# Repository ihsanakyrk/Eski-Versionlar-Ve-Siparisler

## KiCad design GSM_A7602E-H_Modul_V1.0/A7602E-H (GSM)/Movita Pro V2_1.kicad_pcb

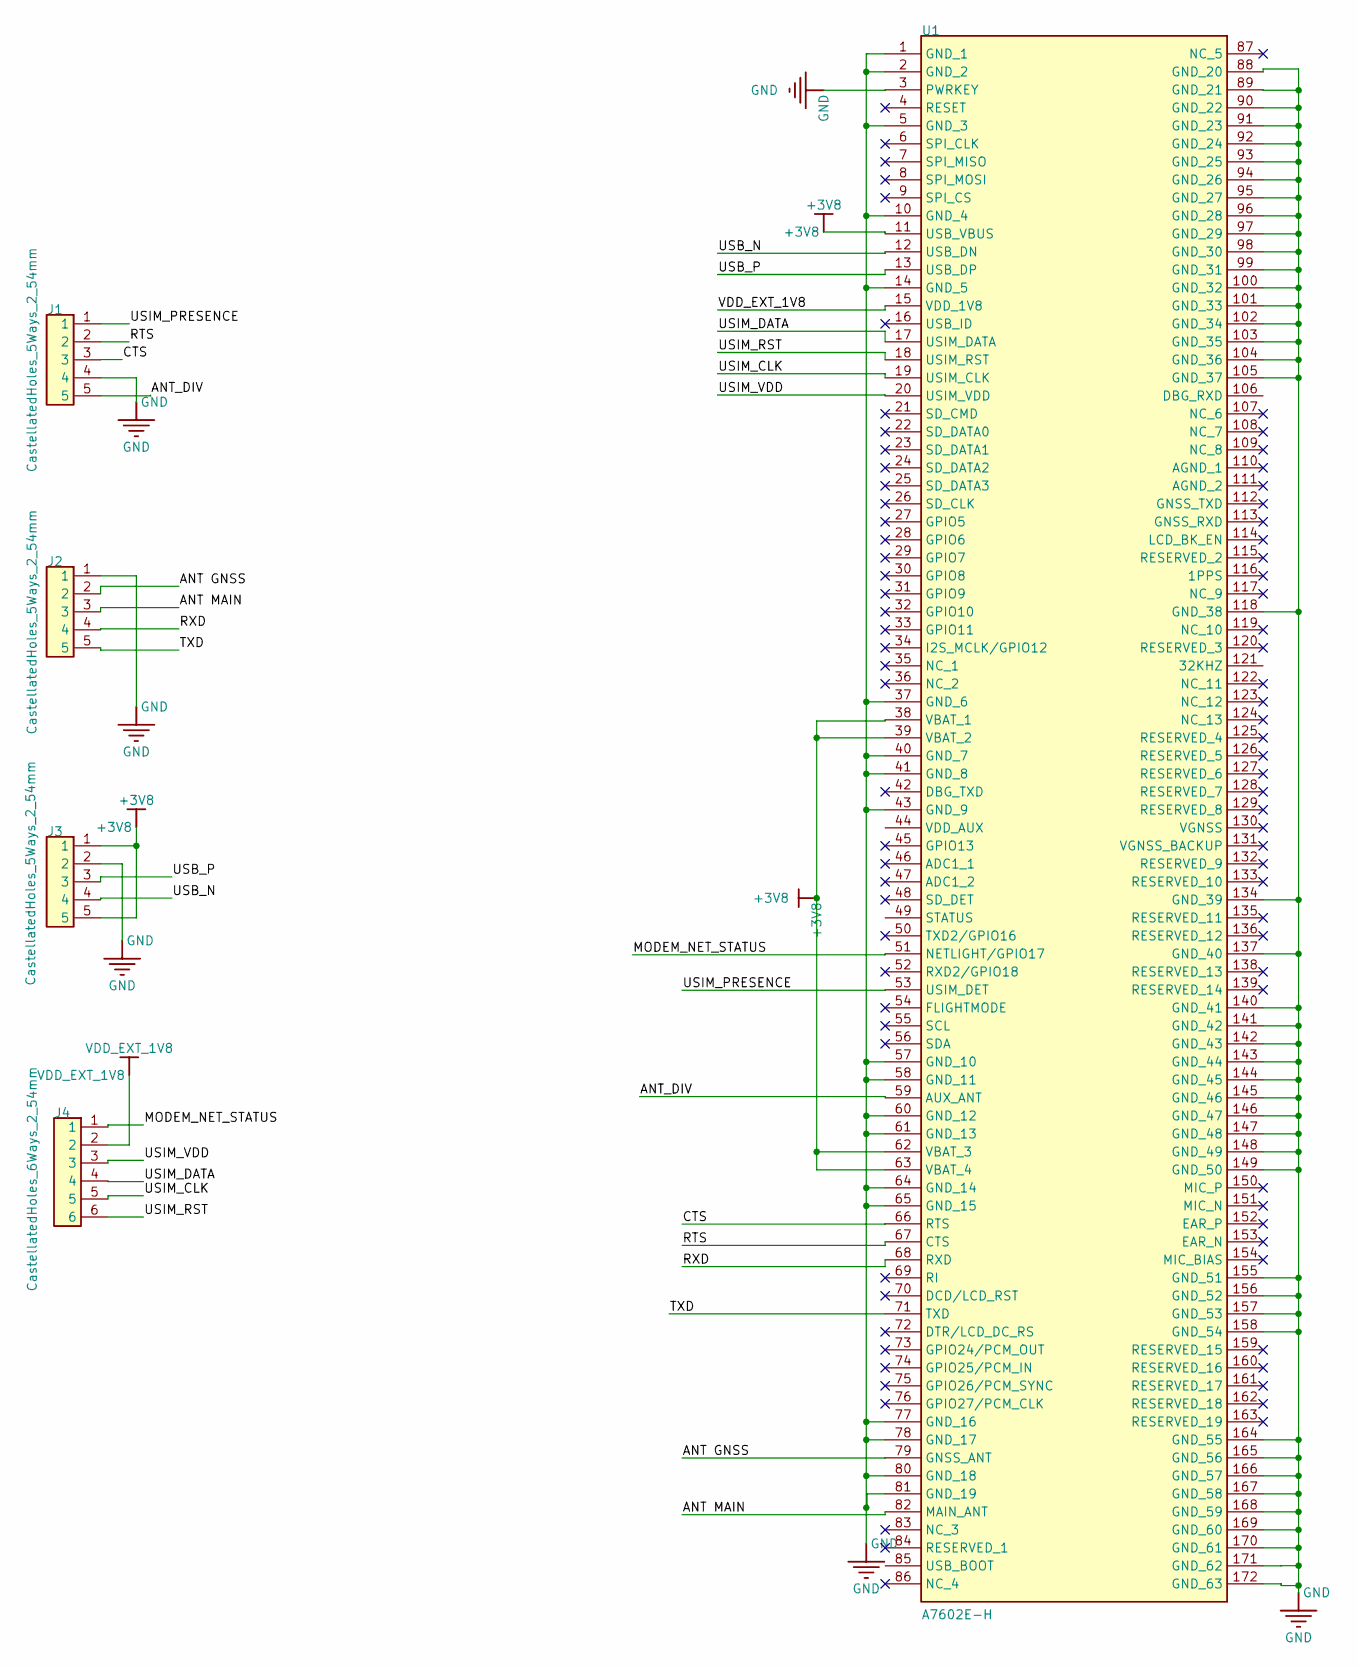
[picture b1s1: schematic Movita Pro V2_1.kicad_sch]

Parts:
J1, J2, J3: CastellatedHoles_5Ways_2_54mm; Castelled Pin Header 1x5 Ways 2.54
J4: CastellatedHoles_6Ways_2_54mm; Castelled Pin Header 1x6 Ways 2.54
U1: A7602E-H; A7602EH; MANUFACTURER_PART_NUMBER A7602E-H; MOUSER PART NUMBER *

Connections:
+3V8: J3.1, J3.5, U1.11 (USB_VBUS), U1.38 (VBAT_1), U1.39 (VBAT_2), U1.62 (VBAT_3), U1.63 (VBAT_4)
/ANT GNSS: J2.2, U1.79 (GNSS_ANT)
/ANT MAIN: J2.3, U1.82 (MAIN_ANT)
/ANT_DIV: J1.5, U1.59 (AUX_ANT)
/CTS: J1.3, U1.66 (RTS)
/MODEM_NET_STATUS: J4.1, U1.51 (NETLIGHT/GPIO17)
/RTS: J1.2, U1.67 (CTS)
/RXD: J2.4, U1.68 (RXD)
/TXD: J2.5, U1.71 (TXD)
/USB_N: J3.4, U1.12 (USB_DN)
/USB_P: J3.3, U1.13 (USB_DP)
/USIM_CLK: J4.5, U1.19 (USIM_CLK)
/USIM_DATA: J4.4, U1.17 (USIM_DATA)
/USIM_PRESENCE: J1.1, U1.53 (USIM_DET)
/USIM_RST: J4.6, U1.18 (USIM_RST)
/USIM_VDD: J4.3, U1.20 (USIM_VDD)
GND: J1.4, J2.1, J3.2, U1.1 (GND_1), U1.2 (GND_2), U1.3 (PWRKEY), U1.5 (GND_3), U1.10 (GND_4), U1.14 (GND_5), U1.37 (GND_6), U1.40 (GND_7), U1.41 (GND_8), U1.43 (GND_9), U1.57 (GND_10), U1.58 (GND_11), U1.60 (GND_12), U1.61 (GND_13), U1.64 (GND_14), U1.65 (GND_15), U1.77 (GND_16), U1.78 (GND_17), U1.80 (GND_18), U1.81 (GND_19), U1.88 (GND_20), U1.89 (GND_21), U1.90 (GND_22), U1.91 (GND_23), U1.92 (GND_24), U1.93 (GND_25), U1.94 (GND_26), U1.95 (GND_27), U1.96 (GND_28), U1.97 (GND_29), U1.98 (GND_30), U1.99 (GND_31), U1.100 (GND_32), U1.101 (GND_33), U1.102 (GND_34), U1.103 (GND_35), U1.104 (GND_36), U1.105 (GND_37), U1.118 (GND_38), U1.134 (GND_39), U1.137 (GND_40), U1.140 (GND_41), U1.141 (GND_42), U1.142 (GND_43), U1.143 (GND_44), U1.144 (GND_45), U1.145 (GND_46), U1.146 (GND_47), U1.147 (GND_48), U1.148 (GND_49), U1.149 (GND_50), U1.155 (GND_51), U1.156 (GND_52), U1.157 (GND_53), U1.158 (GND_54), U1.164 (GND_55), U1.165 (GND_56), U1.166 (GND_57), U1.167 (GND_58), U1.168 (GND_59), U1.169 (GND_60), U1.170 (GND_61), U1.171 (GND_62), U1.172 (GND_63)
VDD_EXT_1V8: J4.2, U1.15 (VDD_1V8)

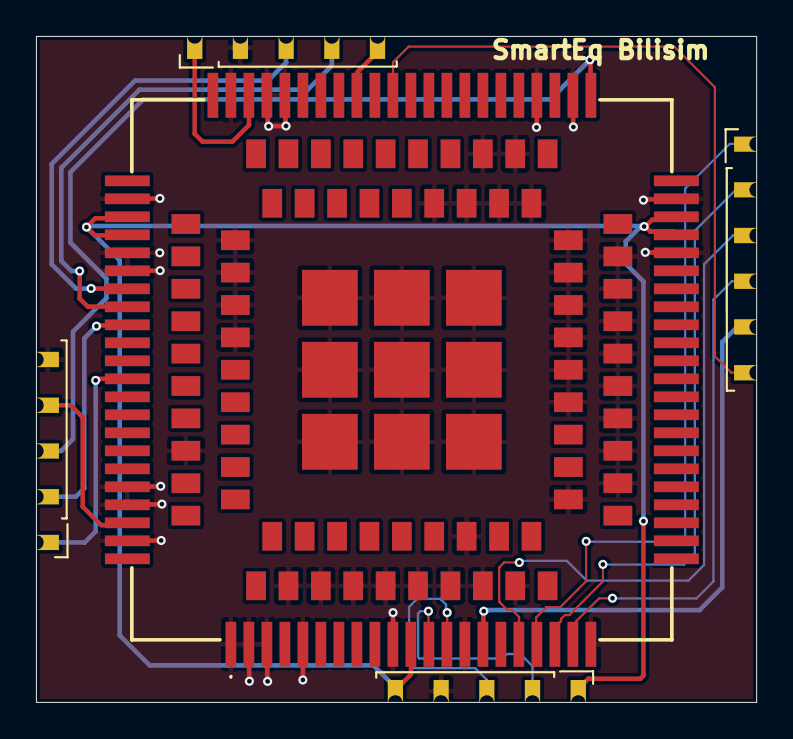
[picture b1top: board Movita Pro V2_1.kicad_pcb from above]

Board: 2 copper layers, 40.0 x 37.0 mm, 5 parts (0 on the bottom side), 18 nets.

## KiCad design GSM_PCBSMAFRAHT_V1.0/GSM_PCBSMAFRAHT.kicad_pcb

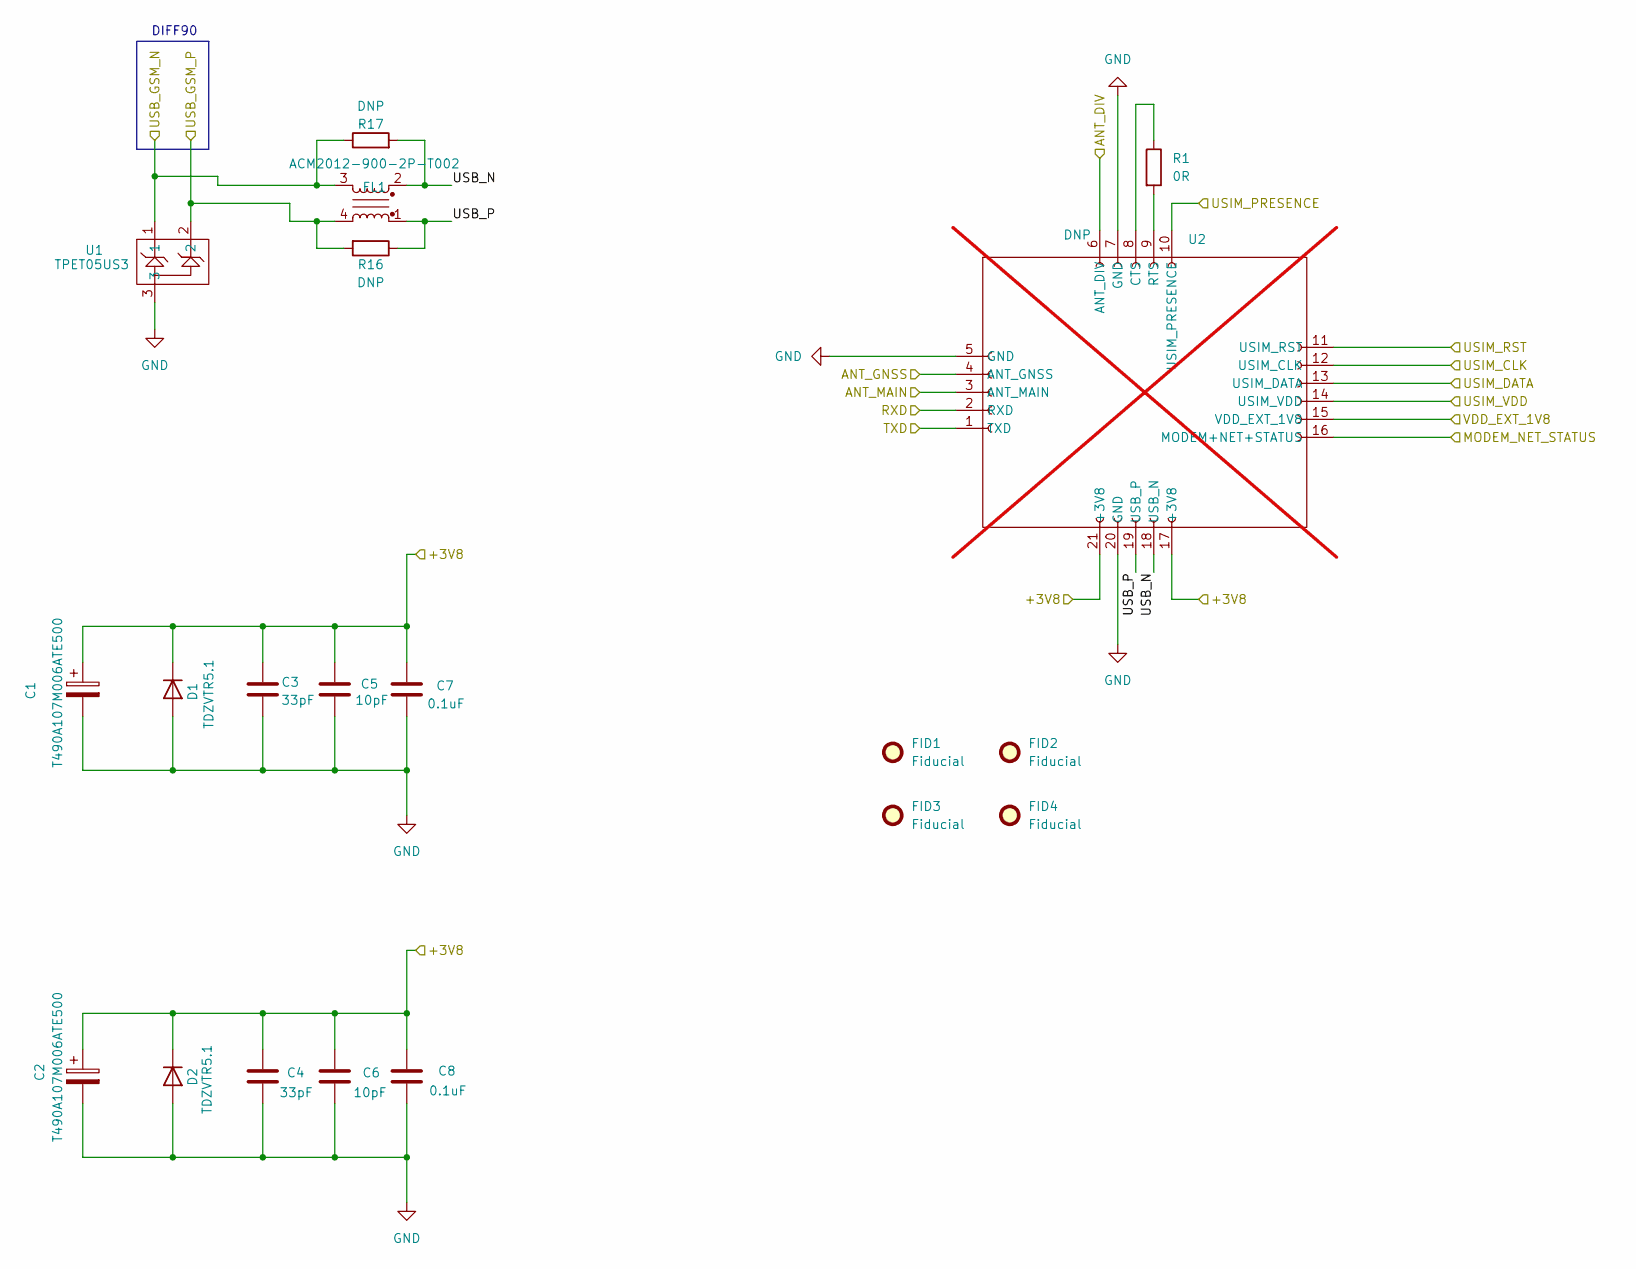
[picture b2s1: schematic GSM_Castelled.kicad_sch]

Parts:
C1, C2: T490A107M006ATE500; T490A; MPN T490A107M006ATE500
C3, C4: 33pF; C_0603_1608Metric
C5, C6: 10pF; C_0603_1608Metric
C7, C8: 0.1uF; C_0603_1608Metric
D1, D2: TDZVTR5.1; MPN TDZVTR5.1
FID1, FID2, FID3, FID4: Fiducial; Fiducial_0.5mm_Mask1.5mm
FL1: ACM2012-900-2P-T002; MPN ACM2012-900-2P-T002
R1: 0R; R_0603_1608Metric
R16, R17: DNP; R_0603_1608Metric
U1: TPET05US3; MPN TPET05US3
U2: DNP; GSM_Castelled; not fitted

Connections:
/91228-3002/MODEM_NET_STATUS: U2.16 (MODEM+NET+STATUS); also elsewhere on the board
/91228-3002/RXD: U2.2 (RXD); also elsewhere on the board
/91228-3002/TXD: U2.1 (TXD); also elsewhere on the board
/91228-3002/USB_GSM_N: FL1.3, R17.1, U1.1; also elsewhere on the board
/91228-3002/USB_GSM_P: FL1.4, R16.2, U1.2; also elsewhere on the board
/91228-3002/USIM_CLK: U2.12 (USIM_CLK); also elsewhere on the board
/91228-3002/USIM_DATA: U2.13 (USIM_DATA); also elsewhere on the board
/91228-3002/USIM_PRESENCE: U2.10 (USIM_PRESENCE); also elsewhere on the board
/91228-3002/USIM_RST: U2.11 (USIM_RST); also elsewhere on the board
/91228-3002/USIM_VDD: U2.14 (USIM_VDD); also elsewhere on the board
/91228-3002/VDD_EXT_1V8: U2.15 (VDD_EXT_1V8); also elsewhere on the board
/GSM_Castelled/+3V8: C1.1, C2.1, C3.1, C4.1, C5.1, C6.1, C7.1, C8.1, D1.1 (K), D2.1 (K), U2.17 (+3V8), U2.21 (+3V8); also elsewhere on the board
/GSM_Castelled/ANT_DIV: U2.6 (ANT_DIV); also elsewhere on the board
/GSM_Castelled/ANT_GNSS: U2.4 (ANT_GNSS); also elsewhere on the board
/GSM_Castelled/ANT_MAIN: U2.3 (ANT_MAIN); also elsewhere on the board
/GSM_Castelled/USB_N: FL1.2, R17.2, U2.18 (USB_N)
/GSM_Castelled/USB_P: FL1.1, R16.1, U2.19 (USB_P)
GND: C1.2, C2.2, C3.2, C4.2, C5.2, C6.2, C7.2, C8.2, D1.2 (A), D2.2 (A), U1.3, U2.5 (GND), U2.7 (GND), U2.20 (GND); also elsewhere on the board
unnamed: R1.1, U2.8 (CTS)
unnamed: R1.2, U2.9 (RTS)

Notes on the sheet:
DIFF90

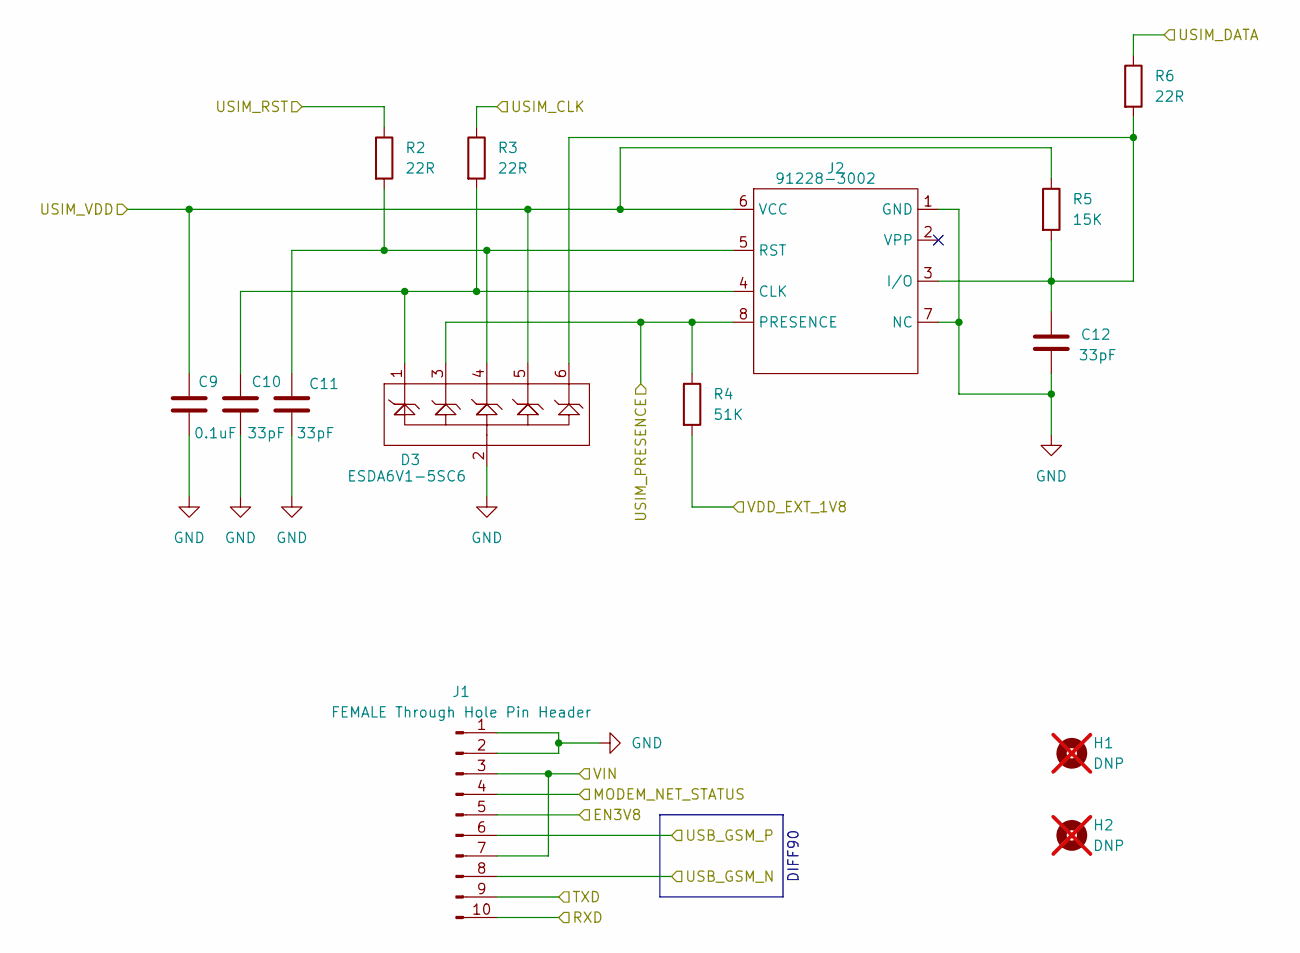
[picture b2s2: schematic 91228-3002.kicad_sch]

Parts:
C9: 0.1uF; C_0603_1608Metric
C10, C11, C12: 33pF; C_0603_1608Metric
D3: ESDA6V1-5SC6; MPN ESDA6V1-5SC6
H1, H2: DNP; Screw_Terminal_1x1; not fitted
J1: FEMALE Through Hole Pin Header; PinHeader_2x05_P2.00mm_Vertical
J2: 91228-3002; 912283002; MPN 91228-3002
R2, R3, R6: 22R; R_0603_1608Metric
R4: 51K; R_0603_1608Metric
R5: 15K; R_0603_1608Metric

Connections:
/91228-3002/EN3V8: J1.5; also elsewhere on the board
/91228-3002/MODEM_NET_STATUS: J1.4; also elsewhere on the board
/91228-3002/RXD: J1.10; also elsewhere on the board
/91228-3002/TXD: J1.9; also elsewhere on the board
/91228-3002/USB_GSM_N: J1.8; also elsewhere on the board
/91228-3002/USB_GSM_P: J1.6; also elsewhere on the board
/91228-3002/USIM_CLK: R3.1; also elsewhere on the board
/91228-3002/USIM_DATA: R6.1; also elsewhere on the board
/91228-3002/USIM_PRESENCE: D3.3, J2.8 (PRESENCE), R4.1; also elsewhere on the board
/91228-3002/USIM_RST: R2.1; also elsewhere on the board
/91228-3002/USIM_VDD: C9.1, D3.5, J2.6 (VCC), R5.1; also elsewhere on the board
/91228-3002/VDD_EXT_1V8: R4.2; also elsewhere on the board
/91228-3002/VIN: J1.3, J1.7; also elsewhere on the board
GND: C9.2, C10.2, C11.2, C12.2, D3.2, J1.1, J1.2, J2.1 (GND), J2.7 (NC); also elsewhere on the board
unnamed: C10.1, D3.1, J2.4 (CLK), R3.2
unnamed: C12.1, D3.6, J2.3 (I/O), R5.2, R6.2
unnamed: C11.1, D3.4, J2.5 (RST), R2.2

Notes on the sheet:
DIFF90

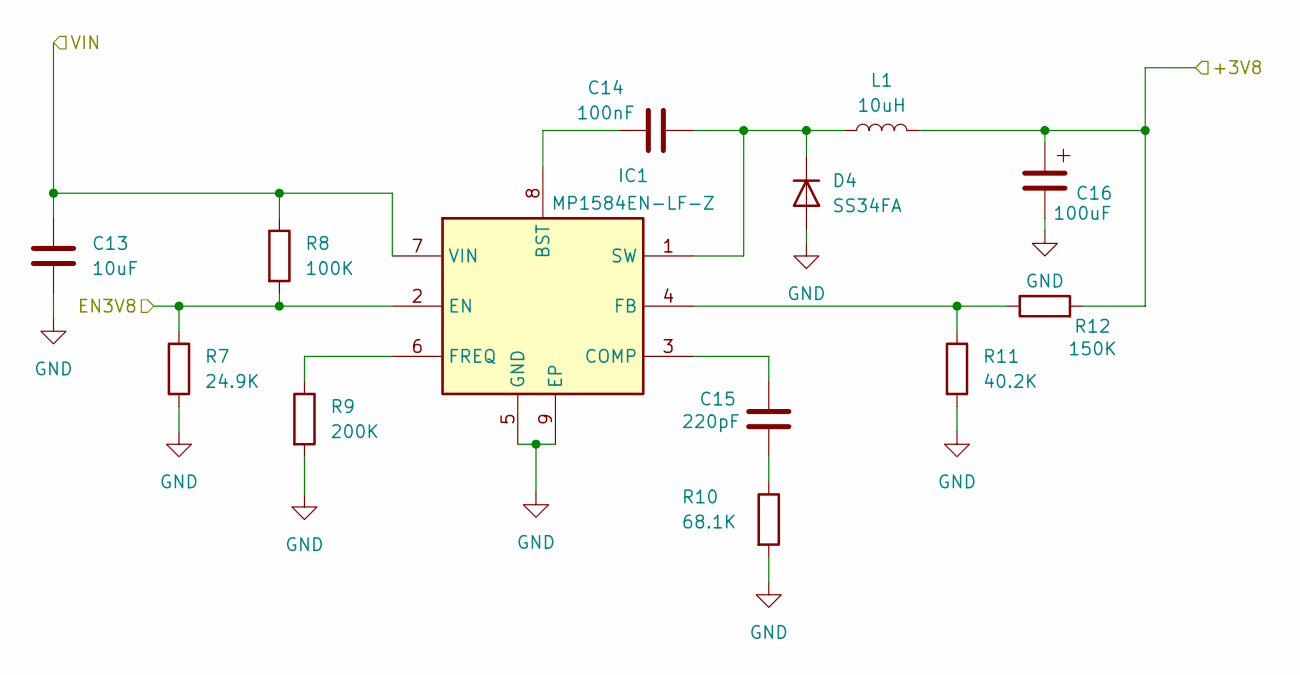
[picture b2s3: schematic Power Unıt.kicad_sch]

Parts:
C13: 10uF; C_1206_3216Metric
C14: 100nF; C_0603_1608Metric
C15: 220pF; C_0603_1608Metric
C16: 100uF; CP_Elec_5x5.4; MPN UWR1A101MCL1GB
D4: SS34FA; SS4FA; MPN SS34FA
IC1: MP1584EN-LF-Z; Manufacturer_Part_Number MP1584EN
L1: 10uH; L_7.3x7.3_H3.5; MPN CDRH74NP-100MC-B
R7: 24.9K; R_0603_1608Metric
R8: 100K; R_0603_1608Metric
R9: 200K; R_0603_1608Metric
R10: 68.1K; R_0603_1608Metric
R11: 40.2K; R_0603_1608Metric
R12: 150K; R_0603_1608Metric

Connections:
/91228-3002/EN3V8: IC1.2 (EN), R7.1, R8.2; also elsewhere on the board
/91228-3002/VIN: C13.1, IC1.7 (VIN), R8.1; also elsewhere on the board
/GSM_Castelled/+3V8: C16.1, L1.2, R12.2; also elsewhere on the board
GND: C13.2, C16.2, D4.2 (A), IC1.5 (GND), IC1.9 (EP), R7.2, R9.2, R10.2, R11.2; also elsewhere on the board
unnamed: C15.2, R10.1
unnamed: C14.2, D4.1 (K), IC1.1 (SW), L1.1
unnamed: C14.1, IC1.8 (BST)
unnamed: C15.1, IC1.3 (COMP)
unnamed: IC1.4 (FB), R11.1, R12.1
unnamed: IC1.6 (FREQ), R9.1

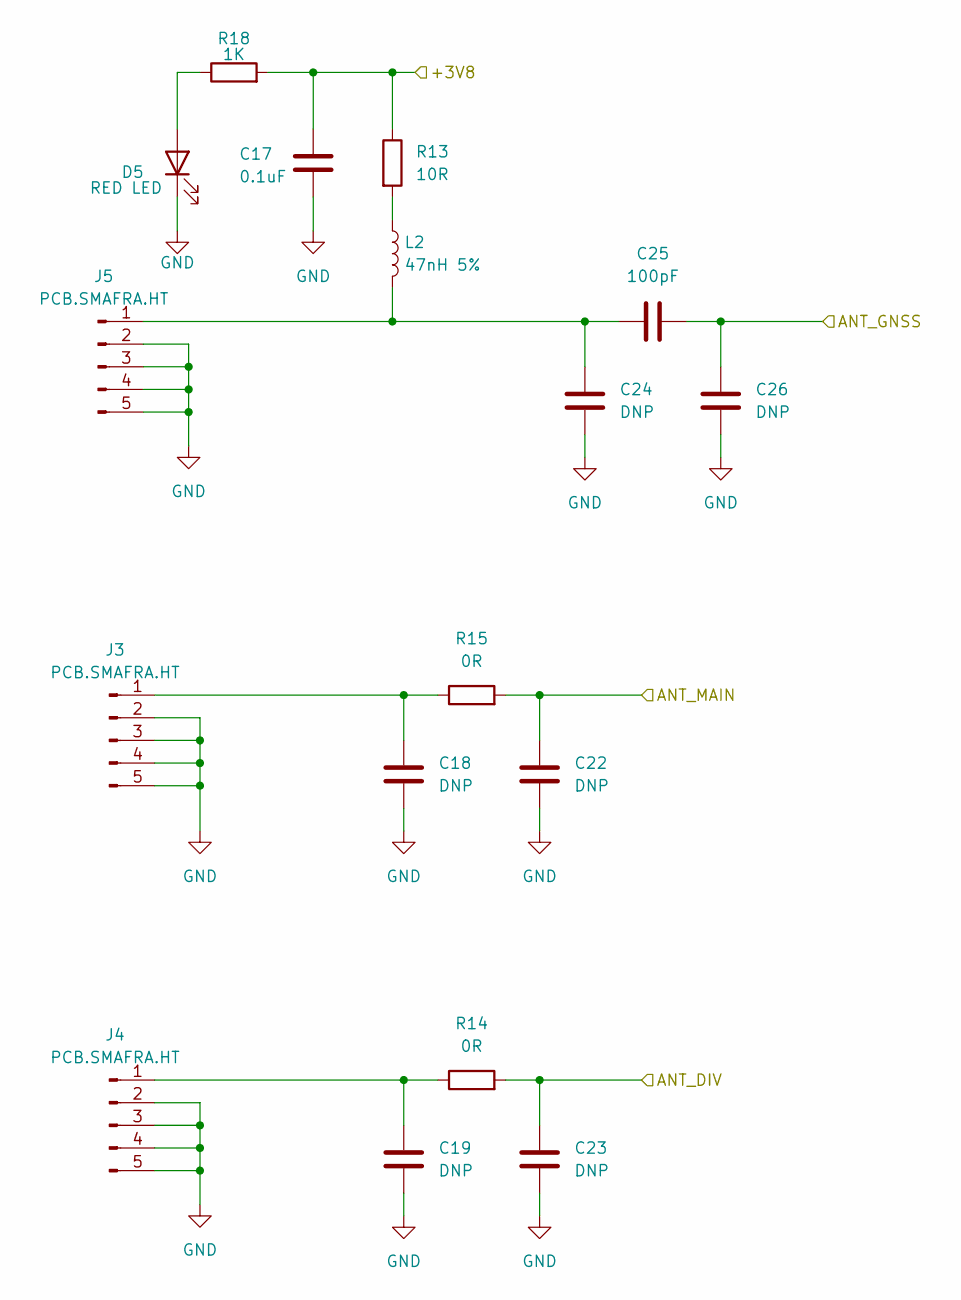
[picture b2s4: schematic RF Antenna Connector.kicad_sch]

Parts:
C17: 0.1uF; C_0603_1608Metric
C18, C19, C22, C23, C24, C26: DNP; C_0603_1608Metric
C25: 100pF; C_0603_1608Metric
D5: RED LED; LED_0805_2012Metric
J3, J4, J5: PCB.SMAFRA.HT; MPN Right angle SMA inner Hole
L2: 47nH 5%; L_0402_1005Metric; MPN LQG15HS47NJ02D
R13: 10R; R_0603_1608Metric
R14, R15: 0R; R_0603_1608Metric
R18: 1K; R_0603_1608Metric

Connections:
/GSM_Castelled/+3V8: C17.1, R13.1, R18.2; also elsewhere on the board
/GSM_Castelled/ANT_DIV: C22.1, R15.2; also elsewhere on the board
/GSM_Castelled/ANT_GNSS: C25.2, C26.1; also elsewhere on the board
/GSM_Castelled/ANT_MAIN: C23.1, R14.2; also elsewhere on the board
GND: C17.2, C18.1, C19.1, C22.2, C23.2, C24.1, C26.2, D5.1 (K), J3.2, J3.3, J3.4, J3.5, J4.2, J4.3, J4.4, J4.5, J5.2, J5.3, J5.4, J5.5; also elsewhere on the board
unnamed: D5.2 (A), R18.1
unnamed: C18.2, J3.1, R15.1
unnamed: C19.2, J4.1, R14.1
unnamed: C24.2, C25.1, J5.1, L2.2
unnamed: L2.1, R13.2

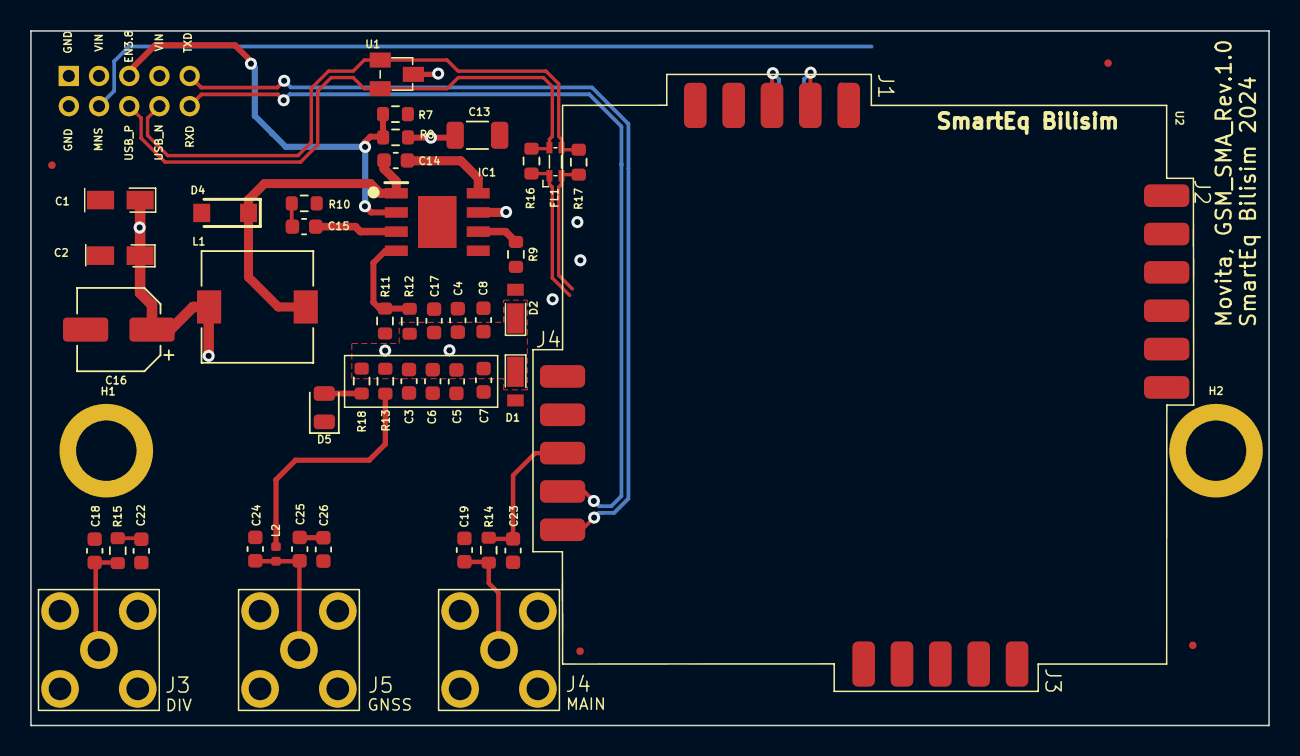
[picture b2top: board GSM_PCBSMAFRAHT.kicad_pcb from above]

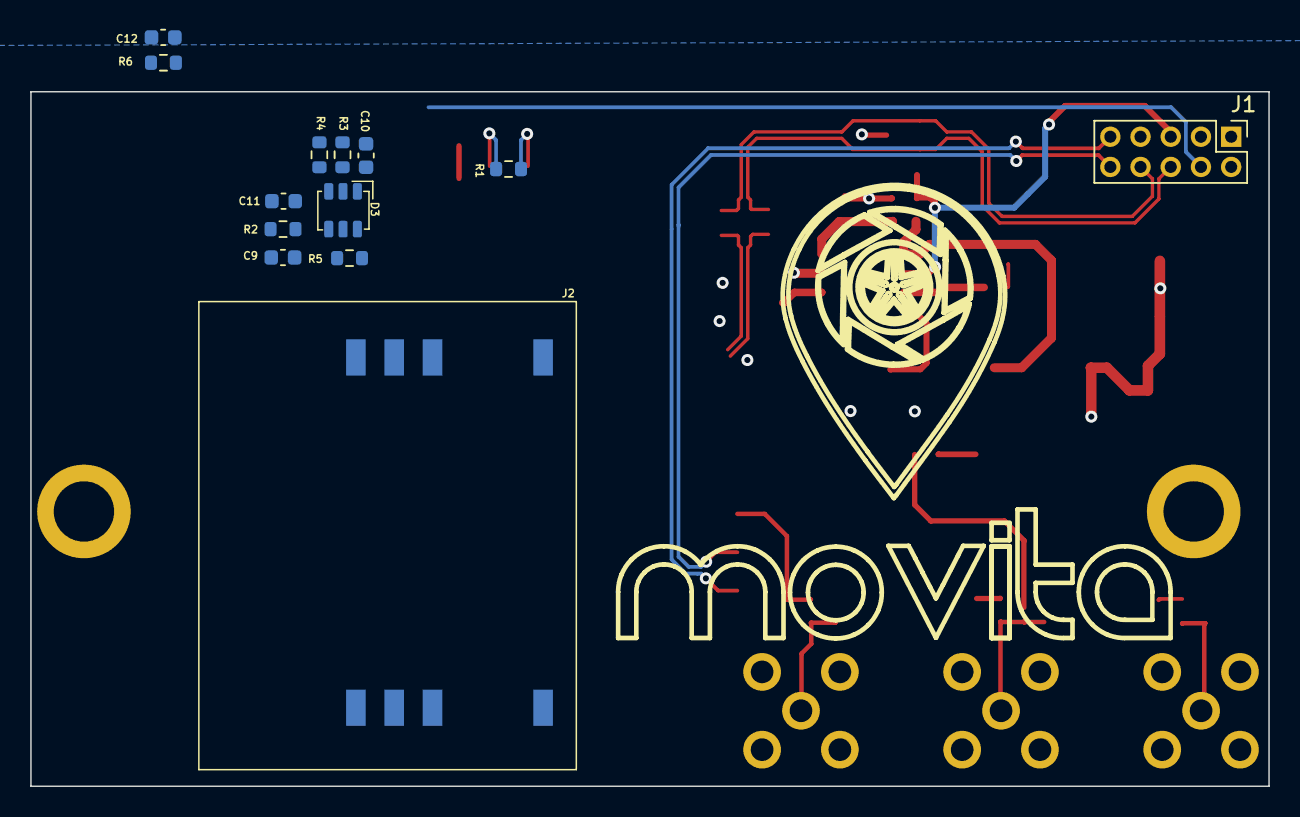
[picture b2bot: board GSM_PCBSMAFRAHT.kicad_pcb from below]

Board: 4 copper layers, 82.0 x 46.0 mm, 64 parts (13 on the bottom side), 36 nets.

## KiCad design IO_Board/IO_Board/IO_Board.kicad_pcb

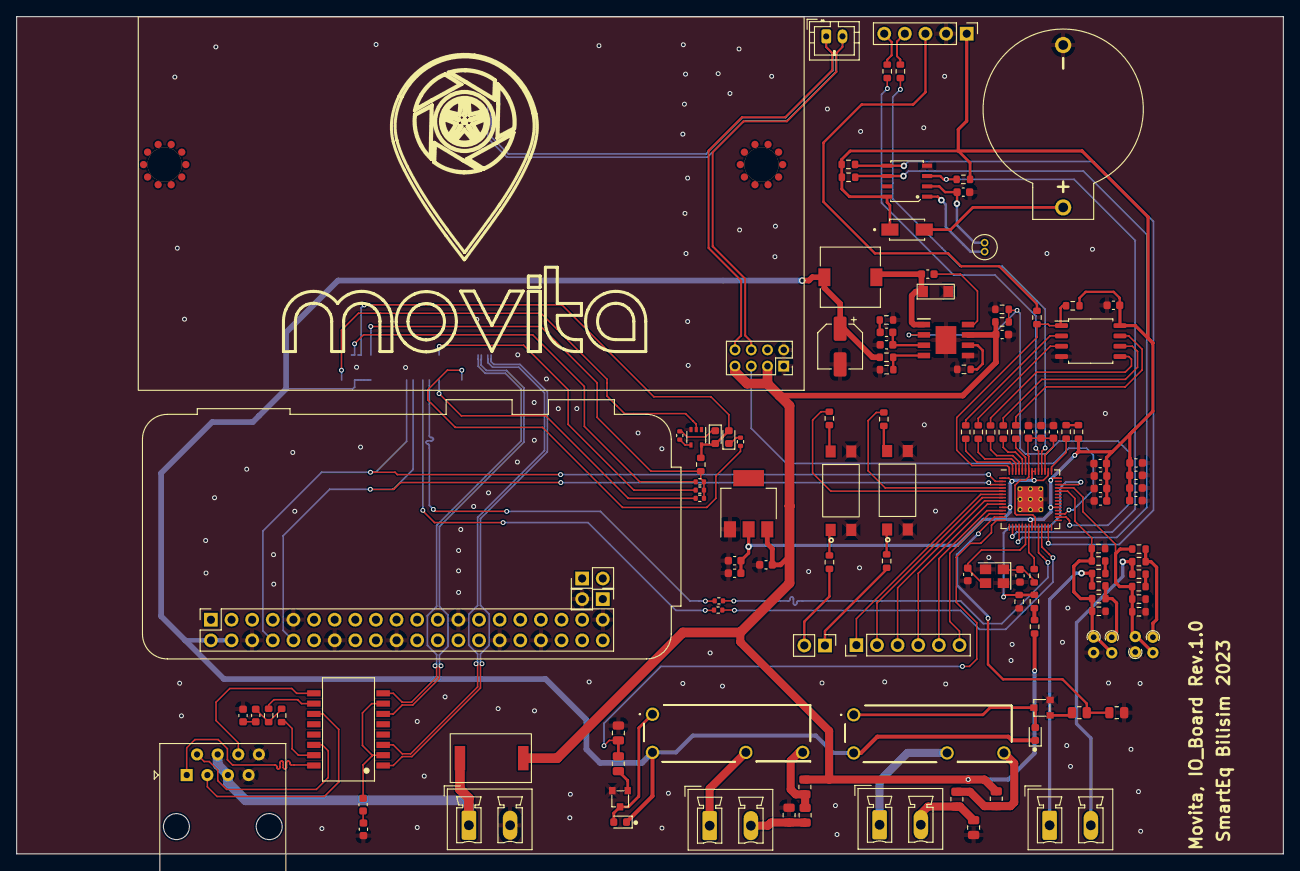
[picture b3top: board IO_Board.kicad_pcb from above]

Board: 2 copper layers, 156.0 x 103.1 mm, 131 parts (1 on the bottom side), 109 nets.

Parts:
C1, C2: 10uF; C_0603_1608Metric
C3, C12, C13, C16, C17, C18, C19, C20, C21, C22: 100nF; C_0603_1608Metric
C4: 150pF; C_0603_1608Metric
C5: DNP; C_0603_1608Metric
C6: 100uF; CP_Elec_5x5.4
C7: 22uF; C_0603_1608Metric
C8: 0.1uF; C_0603_1608Metric
C9: 1nF; C_0603_1608Metric
C10, C11: 27pF; C_0603_1608Metric
C14, C15: 1uF; C_0603_1608Metric
C23: 22pF; C_0603_1608Metric
C24, C25: 0.01uF; C_0603_1608Metric
C26, C27: 1000pF; C_0603_1608Metric
D1: SS34FA
D2: SS14; DIOM4325X250N
D3, D4: MRA4007T3G
D5: LED Green; LED_0603_1608Metric
D6: S6MC
D7: LED Red; LED_0603_1608Metric
IC1: MP1584EN; MP1584
J1: FEMALE Through Hole Pin Header; PinHeader_2x20_P2.54mm_Vertical
J2, J3: DNP; PinHeader_1x02_P2.54mm_Vertical
J4: JST_PH_B2B-PH-K_1x02_P2.00mm_Vertical
J5: FEMALE Through Hole Pin Header; PinHeader_1x02_P2.54mm_Vertical
J6, J8, J14, J15: KF2EDGR-Y-5.08-2P-Right Angle
J7: DNP; PinHeader_1x06_P2.54mm_Vertical
J9: MYOUNG BS-02-A1AJ010
J10, J11: M3x*0.5 L=8; Screw_terminal_shinbo
J12: FEMALE Through Hole Pin Header; PinSocket_2x04_P2.00mm_Vertical
J13: FEMALE Through Hole Pin Header; PinHeader_1x05_P2.54mm_Vertical
J16: RJ45; RJ45_Amphenol_54602-x08_Horizontal
K1, K2: DNP; HF46F_5-HS1
L1: 10uH; L_7.3x7.3_H3.5
Q1, Q2: MMBT2222ALT1G
R1, R2, R3, R4, R25: 1K; R_0603_1608Metric
R5, R6, R53: 0R; R_0603_1608Metric
R7, R8, R23, R55: DNP; R_0603_1608Metric
R9, R10, R15, R16: 100R; R_0603_1608Metric
R11, R13: 1.78K; R_0603_1608Metric
R12, R14: 220R; R_0603_1608Metric
R17: 2.2K; R_0603_1608Metric
R18, R19, R20: 100K; R_0603_1608Metric
R21: 40.2K; R_0603_1608Metric
R22: 210K; R_0603_1608Metric
R24: 10K; R_0603_1608Metric
R26, R27, R28, R29, R30, R33, R34: 27R; R_0603_1608Metric
R31: 200R; R_0603_1608Metric
R32: 1R; R_0603_1608Metric
R35: 4.7K; R_0603_1608Metric
R36, R37: 4.7K %5; R_0603_1608Metric
R38, R39, R44, R45: DNP; R_Axial_DIN0204_L3.6mm_D1.6mm_P1.90mm_Vertical
R40, R48: DNP; R_0805_2012Metric
R41, R42, R49, R50: 0R; R_0805_2012Metric
R43, R62: 1K; R_0402_1005Metric
R46, R51: 10K; R_0805_2012Metric
R47, R52: 1K; R_0805_2012Metric
R54, R63, R64: DNP; R_0402_1005Metric
R56: 725R; R_0603_1608Metric
R57: 275R; R_0603_1608Metric
R58, R60: 75R; R_0603_1608Metric
R59, R61: 2.2K 1%; R_0402_1005Metric
T1: H1102NL
U1, U2: PC817C_4PIN_SMD; PC817C SMD 4pin
U3: LM1117S-3.3; SOT-223
U4: W25Q128JVSIQ; W25Q128JVS
U5: RP2040; RP20400
U6: PCF8563
U7: DNP; Raspberry-Pi-4-Compute-Module
U8: 74LVC1G07SE-7; SOT-353_SC-70-5
Y1: TAXM12M4RLBDDT2T
Y2: ECS-3X8X

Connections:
3.3V: C7.1, C8.1, C9.1, C15.1, C16.1, C17.1, C18.1, C19.1, C20.1, C21.1, C22.1, D2.C, J13.1, R23.1, R31.1, R35.2, R36.2, R37.2, U3.2 (VO), U4.8 (VCC), U5.1 (IOVDD), U5.10 (IOVDD), U5.22 (IOVDD), U5.33 (IOVDD), U5.42 (IOVDD), U5.44 (VREG_IN), U5.48 (USB_VDD), U5.49 (IOVDD), U6.8 (VDD)
5V: C6.1, D3.1 (K), D4.1 (K), J1.2, J1.4, K1.2 (COIL_2), K2.2 (COIL_2), L1.2, R22.2, U7.77 (+5v_(Input)), U7.79 (+5v_(Input)), U7.81 (+5v_(Input)), U7.83 (+5v_(Input)), U7.85 (+5v_(Input)), U7.87 (+5v_(Input))
+1V1: C12.1, C13.1, C14.1, U5.23 (DVDD), U5.45 (VREG_VOUT), U5.50 (DVDD)
/CM4_GPIO/+1.8V: R54.1, U7.88 (+1.8v_(Output)), U7.90 (+1.8v_(Output))
/CM4_GPIO/+3.3v: D5.2 (A), D7.2 (A), R53.2, U7.84 (+3.3v_(Output)), U7.86 (+3.3v_(Output)), U8.5 (VCC)
/CM4_GPIO/CM4_SWCLK: R63.2, U5.24 (SWCLK)
/CM4_GPIO/CM4_SWDIO: R64.2, U5.25 (SWD)
/CM4_GPIO/GPIO_VREF: R53.1, R54.2, R59.1, R61.1, U7.78 (GPIO_VREF(1.8v/3.3v_Input))
/CM4_GPIO/ID_SC: R59.2, U7.35 (ID_SC)
/CM4_GPIO/ID_SD: R61.2, U7.36 (ID_SD)
/CM4_GPIO/USB2_N: J4.1, J12.8, U7.103 (USB2_N)
/CM4_GPIO/USB2_P: J4.2, J12.6, U7.105 (USB2_P)
/CM4_GPIO/VOUT_CAM: D6.2 (A), J8.1, J16.4, J16.5
/CM4_GPIO/nPWR_LED: U7.95 (nPI_LED_PWR), U8.2
/Connectors/Analog_Input1: J6.1, R5.2, R7.2
/Connectors/Analog_Input2: J6.2, R6.2, R8.2
/Connectors/GP4: J7.1, U5.6 (GPIO4)
/Connectors/GP5: J7.2, U5.7 (GPIO5)
/Connectors/GP6: J7.3, U5.8 (GPIO6)
/Connectors/GP7: J7.4, U5.9 (GPIO7)
/Connectors/GP8: J7.5, U5.11 (GPIO8)
/Connectors/GP9: J7.6, U5.12 (GPIO9)
/Connectors/GP26_AO: R9.1, R11.1, R12.1, R15.2, R38.2, R44.1, U5.38 (GPIO26_ADC0)
/Connectors/GP27_AO: R10.1, R13.1, R14.1, R16.2, R39.2, R45.2, U5.39 (GPIO27_ADC1)
/Connectors/GP28_AO: R56.1, R57.1, U5.40 (GPIO28_ADC2)
/Connectors/GP_2: R3.1, U5.4 (GPIO2)
/Connectors/GP_3: R4.1, U5.5 (GPIO3)
/GSM/EN_3.8V: J12.5, U5.31 (GPIO20)
/POWER/EN: IC1.2 (EN), R17.1, R18.2, U5.30 (GPIO19)
/POWER/RTCL 3V3: D2.A, J9.1 (+)
/RP2040/I2C3_SCL_M0: R37.1, U5.18 (GPIO15), U6.6 (SCL)
/RP2040/I2C3_SDA_M0: R36.1, U5.27 (GPIO16), U6.5 (SDA)
/RP2040/QSPI_CSN: R23.2, R24.1, U4.1 (~CS~{}), U5.56 (QSPI_SS)
/RP2040/QSPI_SCLK: R30.2, U4.6 (CLK)
/RP2040/QSPI_SD0: R26.2, U4.5 (DI(IO0))
/RP2040/QSPI_SD1: R27.2, U4.2 (DO(IO1))
/RP2040/QSPI_SD2: R28.2, U4.3 (~WP~{}(IO2))
/RP2040/QSPI_SD3: R29.2, U4.7 (~HOLD~{}/~RESET/~IO3)
/RP2040/RTCIC_INT_L: R35.1, U5.16 (GPIO13), U6.3 (INT)
/RP2040/Relay1_EN: R46.1, R47.2, U5.13 (GPIO10)
/RP2040/Relay2_EN: R51.1, R52.2, U5.14 (GPIO11)
/RP2040/USB D N: J13.4, R34.1
/RP2040/USB D P: J13.5, R33.1
/RP2040/XIN: C10.1, U5.20 (XIN), Y1.3
/RP2040/XOUT: R25.1, U5.21 (XOUT)
/Raspberry Pi Zero/GPIO14: J1.8, U5.2 (GPIO0), U7.55 (GPIO14)
/Raspberry Pi Zero/GPIO15: J1.10, U5.3 (GPIO1), U7.51 (GPIO15)
/Relay/relay output 1: J14.1, K1.3 (NO)
/Relay/relay output 2: J15.1, K2.3 (NO)
ADC_VREF: R31.2, R32.1
GND: C1.2, C2.2, C5.2, C6.2, C7.2, C8.2, C9.2, C10.2, C11.2, C12.2, C13.2, C14.2, C15.2, C16.2, C17.2, C18.2, C19.2, C20.2, C21.2, C22.2, C23.2, C25.2, C27.2, D1.2 (A), IC1.5 (GND), IC1.9 (EP), J1.6, J1.9, J1.14, J1.20, J1.25, J1.30, J1.34, J1.39, J3.2, J8.2, J9.2 (-), J12.1, J12.2, J13.2, J16.7, J16.8, Q1.2 (E), Q2.2 (E), R12.2, R14.2, R15.1, R16.1, R17.2, R19.2, R20.2, R21.2, R41.1, R44.2, R45.1, R46.2, R50.1, R51.2, R57.2, U1.2 (K), U1.3 (E), U2.2 (K), U2.3 (E), U3.1 (ADJ), U4.4 (GND), U5.19 (TESTEN), U5.57 (GND), U6.4 (VSS), U7.1 (GND), U7.2 (GND), U7.7 (GND), U7.8 (GND), U7.13 (GND), U7.14 (GND), U7.22 (GND), U7.23 (GND), U7.32 (GND), U7.33 (GND), U7.42 (GND), U7.43 (GND), U7.52 (GND), U7.53 (GND), U7.59 (GND), U7.60 (GND), U7.65 (GND), U7.66 (GND), U7.71 (GND), U7.74 (GND), U7.98 (GND), U7.107 (GND), U7.108 (GND), U7.113 (GND), U7.114 (GND), U7.119 (GND), U7.120 (GND), U7.125 (GND), U7.126 (GND), U7.131 (GND), U7.132 (GND), U7.137 (GND), U7.138 (GND), U7.144 (GND), U7.150 (GND), U7.155 (GND), U7.156 (GND), U7.161 (GND), U7.162 (GND), U7.167 (GND), U7.168 (GND), U7.173 (GND), U7.174 (GND), U7.179 (GND), U7.180 (GND), U7.185 (GND), U7.186 (GND), U7.191 (GND), U7.192 (GND), U7.197 (GND), U7.198 (GND), U8.3 (GND), Y1.2, Y1.4
unnamed: C4.2, R20.1
unnamed: C11.1, R25.2, Y1.1
unnamed: C24.2, C25.1
unnamed: C26.1, R58.1, R60.1
unnamed: C26.2, C27.1
unnamed: C3.2, D1.1 (K), IC1.1 (SW), L1.1
unnamed: D3.2 (A), K1.1 (COIL_1), Q1.3 (C)
unnamed: D4.2 (A), K2.1 (COIL_1), Q2.3 (C)
unnamed: D5.1 (K), R43.1
unnamed: D7.1 (K), R62.1
unnamed: C3.1, IC1.8 (BST)
unnamed: C4.1, C5.1, IC1.3 (COMP)
unnamed: IC1.4 (FB), R21.1, R22.1
unnamed: IC1.6 (FREQ), R19.1
unnamed: J5.1, R1.1
unnamed: J5.2, R2.1
unnamed: J13.3, R24.2
unnamed: J14.2, R48.1, R50.2
unnamed: J15.2, R40.2, R41.2
unnamed: K1.4 (COM), R48.2, R49.2
unnamed: K2.4 (COM), R40.1, R42.1
unnamed: Q1.1 (B), R47.1
unnamed: Q2.1 (B), R52.1
unnamed: R6.1, R10.2, R39.1
unnamed: R7.1, R11.2
unnamed: R8.1, R13.2
unnamed: R5.1, R9.2, R38.1
unnamed: R55.2, R56.2
unnamed: R62.2, U8.4
unnamed: C24.1, T1.2 (CT1), T1.7 (CT2)
unnamed: R58.2, T1.10 (CT3)
unnamed: R60.2, T1.15 (CT4)
unnamed: R1.2, U1.1 (A)
unnamed: R3.2, U1.4 (C)
unnamed: R2.2, U2.1 (A)
unnamed: R4.2, U2.4 (C)
unnamed: R32.2, U5.43 (ADC_AVDD)
unnamed: R30.1, U5.52 (QSPI_SCLK)
unnamed: R26.1, U5.53 (QSPI_SD0)
unnamed: R27.1, U5.55 (QSPI_SD1)
unnamed: R28.1, U5.54 (QSPI_SD2)
unnamed: R29.1, U5.51 (QSPI_SD3)
unnamed: R34.2, U5.46 (USB_DM)
unnamed: R33.2, U5.47 (USB_DP)
unnamed: U6.1 (OSCI), Y2.1
unnamed: C23.1, U6.2 (OSCO), Y2.2
unnamed: R64.1, U7.45 (GPIO24)
unnamed: R63.1, U7.41 (GPIO25)
unnamed: R43.2, U7.21 (PI_nLED_Activity)
RX_N: T1.8 (RD-), U7.12 (Ethernet_Pair0_P)
RX_P: T1.6 (RD+), U7.10 (Ethernet_Pair0_N)
TRD0_N: J16.2, T1.14 (TX-)
TRD0_P: J16.1, T1.16 (TX+)
TRD1_N: J16.6, T1.9 (RX-)
TRD1_P: J16.3, T1.11 (RX+)
TX_N: T1.3 (TD-), U7.6 (Ethernet_Pair1_N)
TX_P: T1.1 (TD+), U7.4 (Ethernet_Pair1_P)
VIN: C1.1, C2.1, D6.1 (K), IC1.7 (VIN), J12.3, J12.7, R18.1, R42.2, R49.1, R55.1, U3.3 (VI)

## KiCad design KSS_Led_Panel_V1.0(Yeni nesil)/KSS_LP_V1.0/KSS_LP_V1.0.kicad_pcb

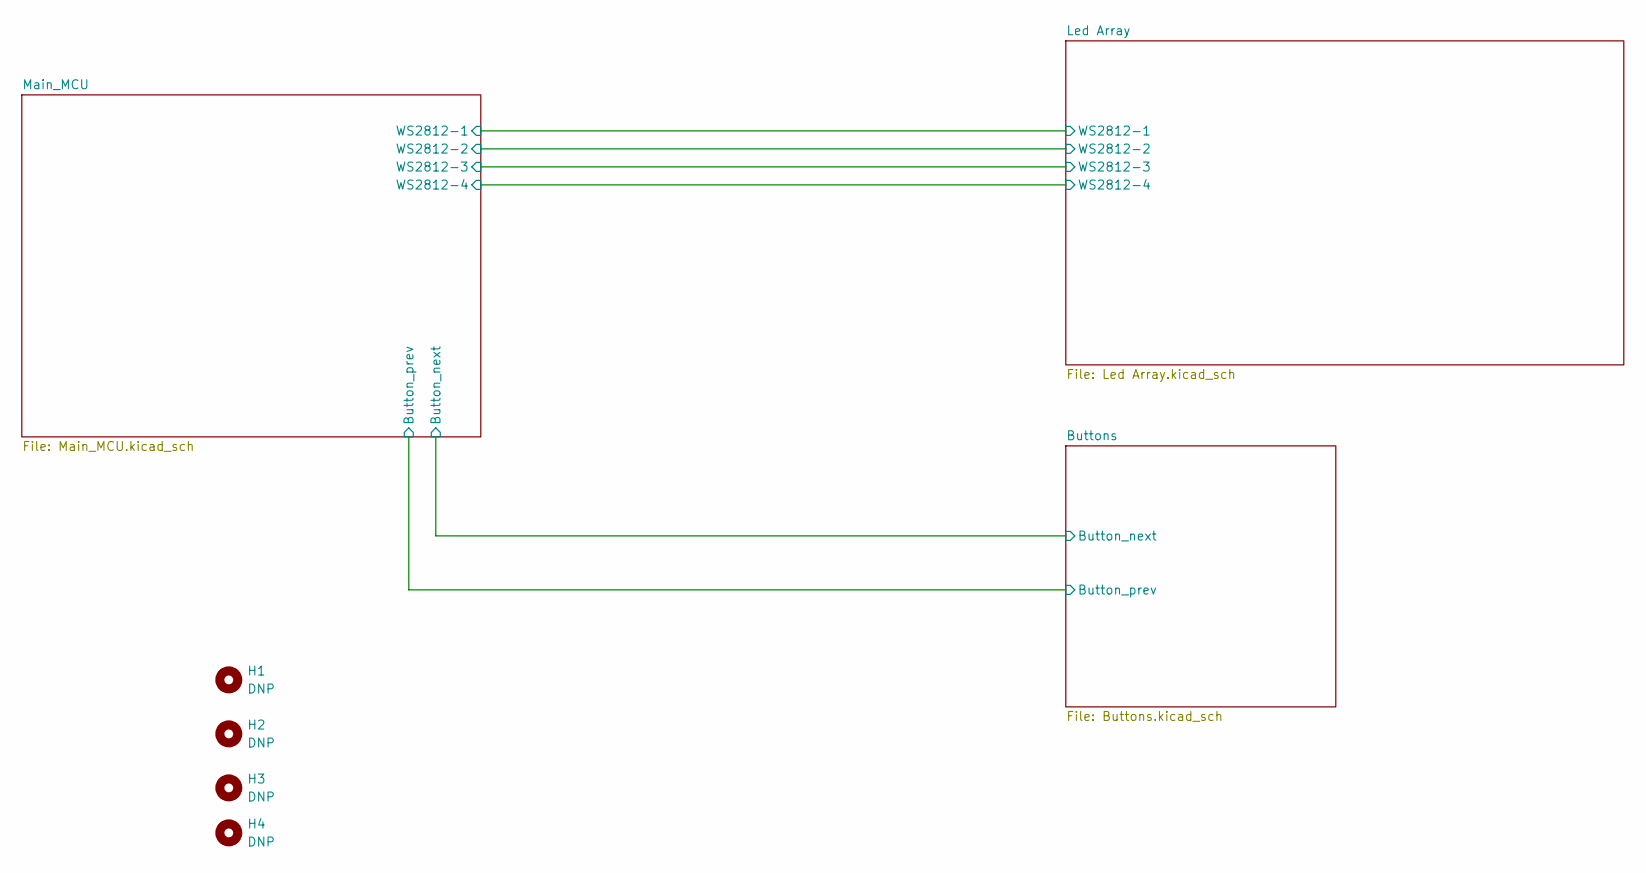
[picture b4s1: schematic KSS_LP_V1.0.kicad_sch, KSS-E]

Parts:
H1, H2, H3, H4: DNP; MountingHole_3mm

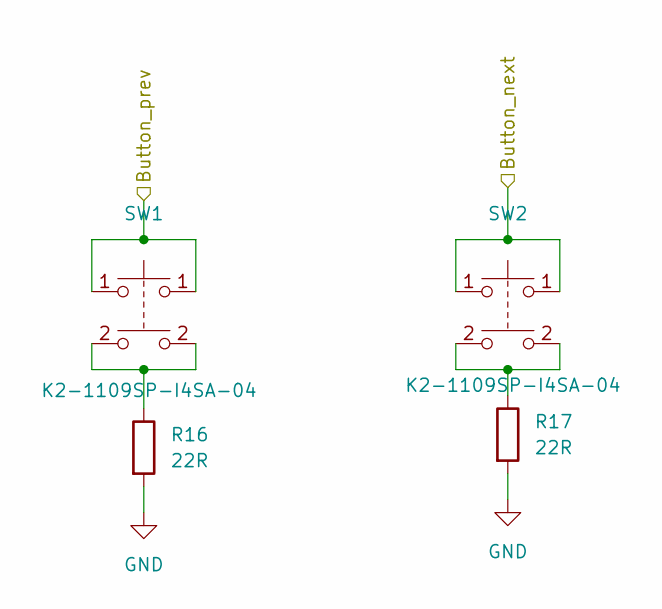
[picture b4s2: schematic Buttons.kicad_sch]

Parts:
R16, R17: 22R; R_0603_1608Metric
SW1, SW2: K2-1109SP-I4SA-04

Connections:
/Main_MCU/GPIO2: SW1.1; also elsewhere on the board
/Main_MCU/GPIO3: SW2.1; also elsewhere on the board
GND: R16.2, R17.2; also elsewhere on the board
unnamed: R16.1, SW1.2
unnamed: R17.1, SW2.2
